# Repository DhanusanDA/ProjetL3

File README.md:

# ProjetL3
Projet de Robotique L3
Cette branche contient les conceptions 3D faites sur SolidWorks pour la structure du robot. Il contient les pièces de support de capteurs et la roue codeuse

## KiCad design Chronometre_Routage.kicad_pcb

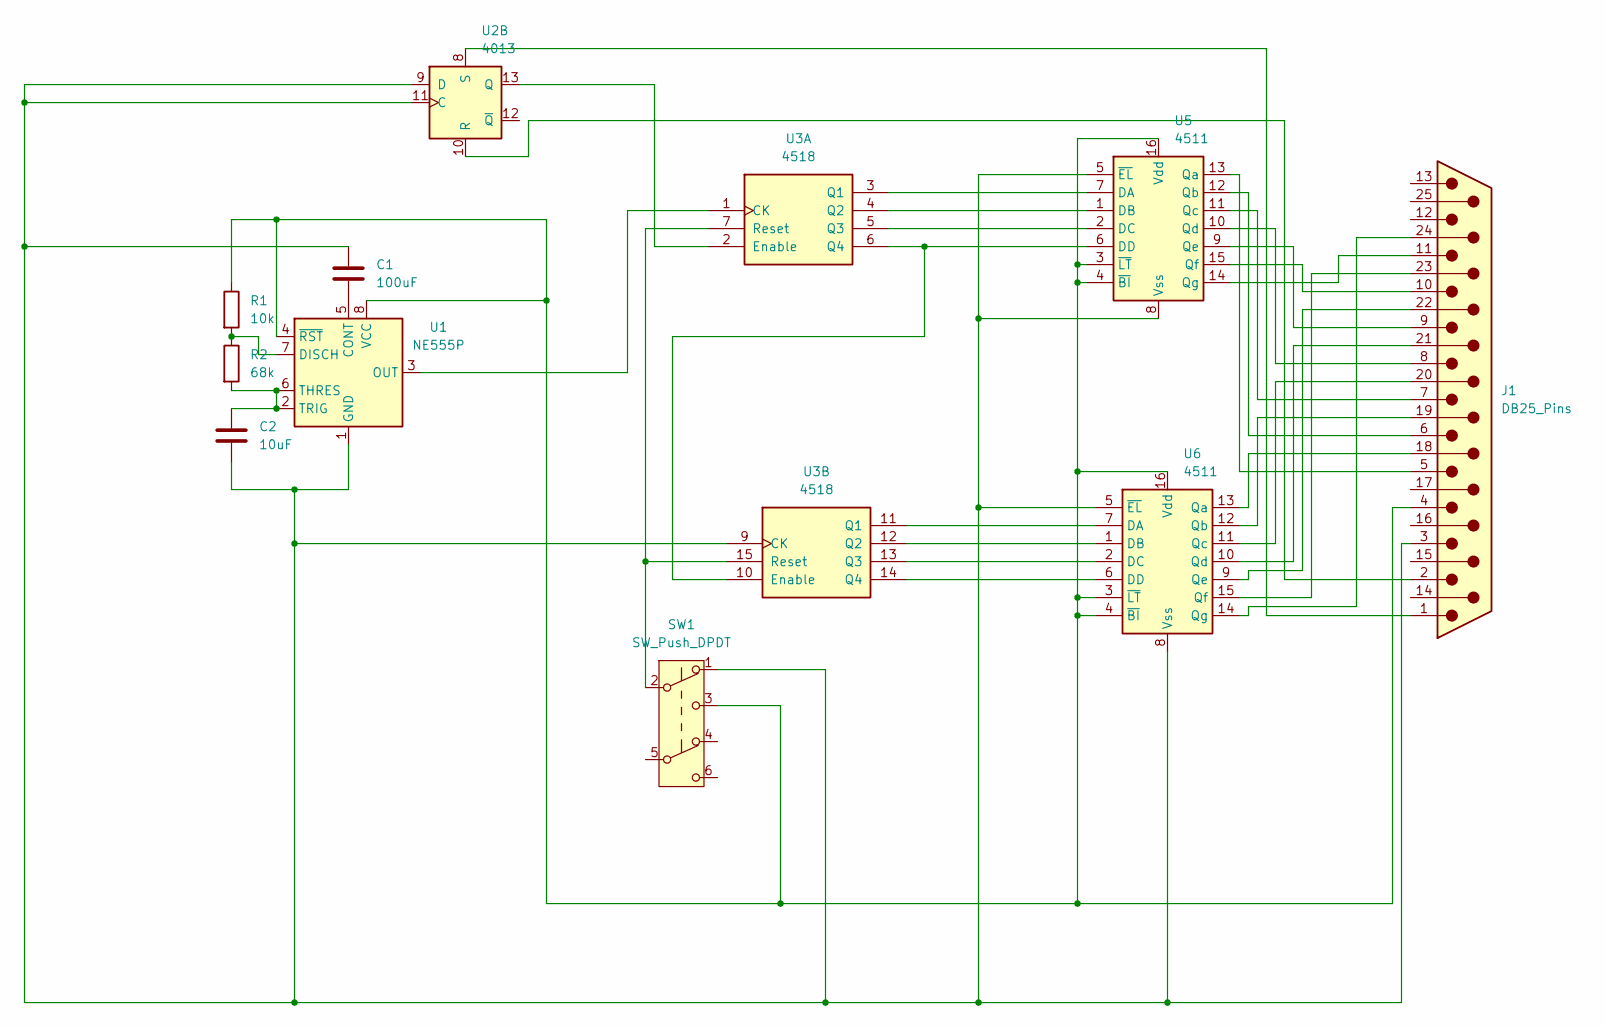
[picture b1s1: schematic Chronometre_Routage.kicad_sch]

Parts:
C1: 100uF; CP_Axial_L10.0mm_D6.0mm_P15.00mm_Horizontal
C2: 10uF; CP_Axial_L10.0mm_D6.0mm_P15.00mm_Horizontal
J1: DB25_Pins; DSUB-25_Socket_Horizontal_P2.77x2.84mm_EdgePinOffset4.94mm_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
R1: 10k; R_Axial_DIN0411_L9.9mm_D3.6mm_P7.62mm_Vertical
R2: 68k; R_Axial_DIN0411_L9.9mm_D3.6mm_P7.62mm_Vertical
SW1: SW_Push_DPDT; SWITCH
U1: NE555P; DIP-8_W7.62mm
U2: 4013; DIP-14_W7.62mm
U3: 4518; DIP-16_W7.62mm
U5, U6: 4511; DIP-16_W7.62mm

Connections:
unnamed: J1.18, U6.13 (Qa)
unnamed: J1.19, U6.12 (Qb)
unnamed: J1.20, U6.11 (Qc)
unnamed: J1.21, U6.10 (Qd)
unnamed: J1.22, U6.9 (Qe)
unnamed: J1.23, U6.15 (Qf)
unnamed: J1.24, U6.14 (Qg)
unnamed: C1.2, U1.5 (CONT)
unnamed: R1.2, R2.1, U1.7 (DISCH)
unnamed: C1.1, C2.2, J1.3, SW1.1 (A), U1.1 (GND), U2.9 (D), U2.11 (C), U3.9 (CK), U5.5 (~EL), U5.8 (Vss), U6.5 (~EL), U6.8 (Vss)
unnamed: U1.3 (OUT), U3.1 (CK)
unnamed: C2.1, R2.2, U1.2 (TRIG), U1.6 (THRES)
unnamed: J1.4, R1.1, SW1.3 (C), U1.4 (~RST), U1.8 (VCC), U5.3 (~LT), U5.4 (~BI), U5.16 (Vdd), U6.3 (~LT), U6.4 (~BI), U6.16 (Vdd)
unnamed: U2.13 (Q), U3.2 (Enable)
unnamed: J1.2, U2.10 (R)
unnamed: J1.1, U2.8 (S)
unnamed: U3.3 (Q1), U5.7 (DA)
unnamed: U3.4 (Q2), U5.1 (DB)
unnamed: U3.5 (Q3), U5.2 (DC)
unnamed: U3.6 (Q4), U3.10 (Enable), U5.6 (DD)
unnamed: SW1.2 (B), U3.7 (Reset), U3.15 (Reset)
unnamed: U3.11 (Q1), U6.7 (DA)
unnamed: U3.12 (Q2), U6.1 (DB)
unnamed: U3.13 (Q3), U6.2 (DC)
unnamed: U3.14 (Q4), U6.6 (DD)
unnamed: J1.5, U5.13 (Qa)
unnamed: J1.6, U5.12 (Qb)
unnamed: J1.7, U5.11 (Qc)
unnamed: J1.8, U5.10 (Qd)
unnamed: J1.9, U5.9 (Qe)
unnamed: J1.10, U5.15 (Qf)
unnamed: J1.11, U5.14 (Qg)

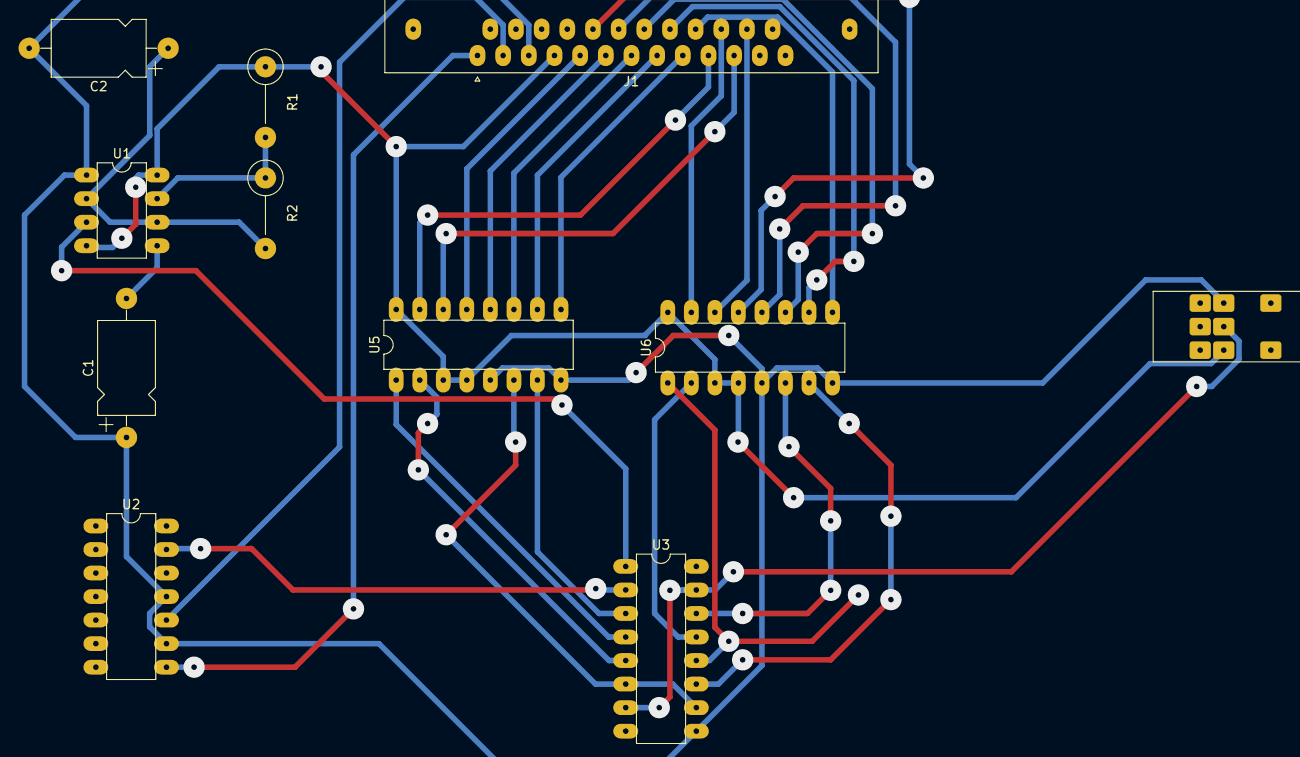
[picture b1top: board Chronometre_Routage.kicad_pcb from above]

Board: 2 copper layers, 11 parts (0 on the bottom side), 32 nets.

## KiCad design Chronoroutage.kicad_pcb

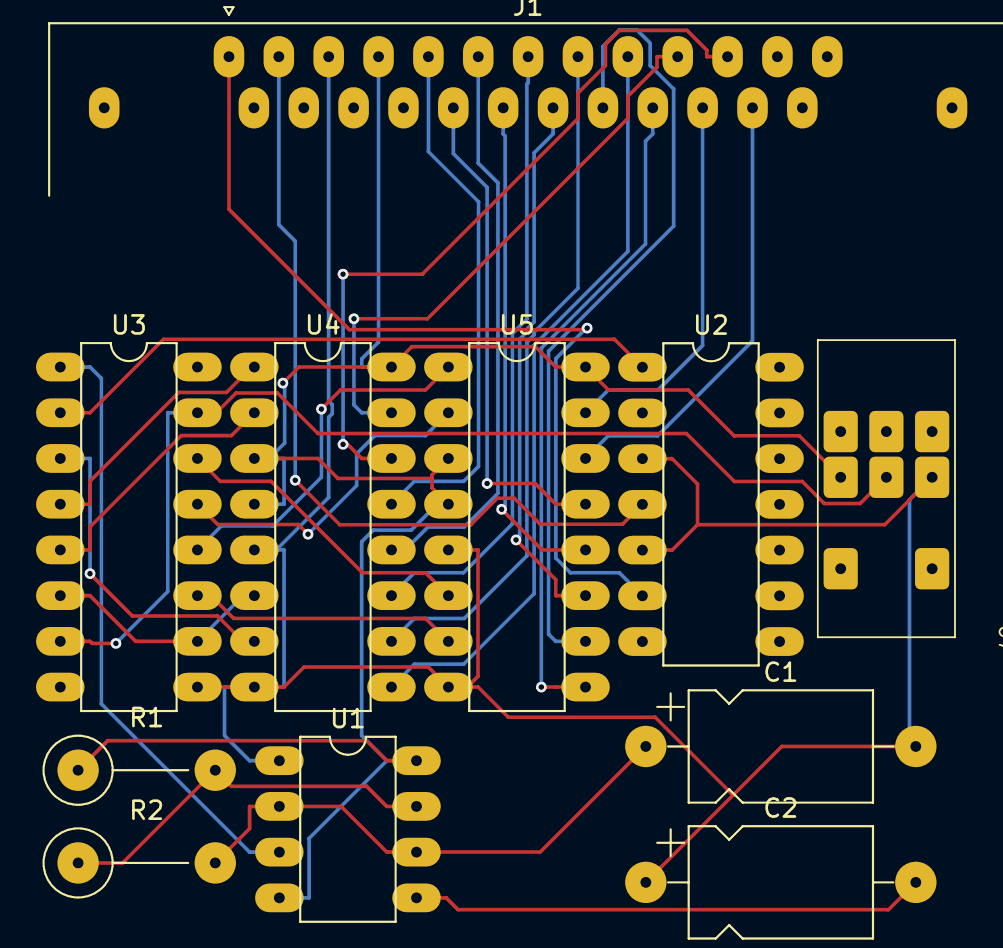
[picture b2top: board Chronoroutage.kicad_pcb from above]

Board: 2 copper layers, 11 parts (0 on the bottom side), 32 nets.

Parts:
C1, C2: 100uF; CP_Axial_L10.0mm_D6.0mm_P15.00mm_Horizontal
J1: DB25_Pins; DSUB-25_Pins_Horizontal_P2.77x2.84mm_EdgePinOffset4.94mm_Ho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
R1: 10k; R_Axial_DIN0411_L9.9mm_D3.6mm_P7.62mm_Vertical
R2: 68k; R_Axial_DIN0411_L9.9mm_D3.6mm_P7.62mm_Vertical
SW1: SW_Push_DPDT; SWITCH
U1: NE555P; DIP-8_W7.62mm
U2: 4013; DIP-14_W7.62mm
U3: 4518; DIP-16_W7.62mm
U4, U5: 4511; DIP-16_W7.62mm

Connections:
+8V: J1.4, R1.1, SW1.3 (C), U1.4 (~RST), U1.8 (VCC), U4.3 (~LT), U4.4 (~BI), U4.16 (Vdd), U5.3 (~LT), U5.4 (~BI), U5.16 (Vdd)
GND: C1.2, C2.1, J1.3, SW1.1 (A), U1.1 (GND), U2.3 (C), U2.5 (D), U3.9 (CK), U4.5 (~EL), U4.8 (Vss), U5.5 (~EL), U5.8 (Vss)
unnamed: J1.18, U5.13 (Qa)
unnamed: J1.19, U5.12 (Qb)
unnamed: J1.20, U5.11 (Qc)
unnamed: J1.21, U5.10 (Qd)
unnamed: J1.22, U5.9 (Qe)
unnamed: J1.23, U5.15 (Qf)
unnamed: J1.24, U5.14 (Qg)
unnamed: C2.2, U1.5 (CONT)
unnamed: R1.2, R2.1, U1.7 (DISCH)
unnamed: U1.3 (OUT), U3.1 (CK)
unnamed: C1.1, R2.2, U1.2 (TRIG), U1.6 (THRES)
unnamed: U2.1 (Q), U3.2 (Enable)
unnamed: J1.2, U2.4 (R)
unnamed: J1.1, U2.6 (S)
unnamed: U3.3 (Q1), U4.7 (DA)
unnamed: U3.4 (Q2), U4.1 (DB)
unnamed: U3.5 (Q3), U4.2 (DC)
unnamed: U3.6 (Q4), U3.10 (Enable), U4.6 (DD)
unnamed: SW1.2 (B), U3.7 (Reset), U3.15 (Reset)
unnamed: U3.11 (Q1), U5.7 (DA)
unnamed: U3.12 (Q2), U5.1 (DB)
unnamed: U3.13 (Q3), U5.2 (DC)
unnamed: U3.14 (Q4), U5.6 (DD)
unnamed: J1.5, U4.13 (Qa)
unnamed: J1.6, U4.12 (Qb)
unnamed: J1.7, U4.11 (Qc)
unnamed: J1.8, U4.10 (Qd)
unnamed: J1.9, U4.9 (Qe)
unnamed: J1.10, U4.15 (Qf)
unnamed: J1.11, U4.14 (Qg)

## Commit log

2026-05-15 Add files via upload
    Ce fichier ;pcb correspond au typon de la carte à tirer. Il a été effectuée avec Free Routing.
2026-05-16 Add files via upload
    Ce nouveau fichier correspond au routage de notre montage manuellement. Comparé à l'ancien fichier, le routage n'a pas été fait par logiciel. J'attend la decision du professeur afin de savoir lequel 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
2026-05-16 Add files via upload
    Ce fichier est le Schematic du montage qui correspond au chronométrage avec le logiciel KiCad. Ce montage a directement été validé par les intervenants. Il correspond a mon montage déjà effectué sur 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
2026-05-18 Add files via upload
    Code pour le suivi de ligne
2026-05-19 changement
    Modification du système de vitesse ajout de petite et grande vitesse pour gérer le suivi de ligne et les virages
2026-05-20 Add files via upload
    Ajout de programme de gestion ultrasons et servomoteur
2026-05-20 Create Evitement_Obstacle_SuiviLigne
    Le premier code pour l'evitement d'obstacle avec le suivi de ligne
2026-05-20 Create Evitement_Obstacle
    Programme pour l'évitement d'obstacle, il complète le précedent
2026-05-21 Add files via upload
    Chrono validé le 20/05/2026
2026-05-21 Squelette V1
    Ajout du squelette du programme du robot suiveur de ligne + implémentation des fonction : suivi de ligne, détection de couleur, traversée du tunnel et pilotage du moteur
2026-05-21 Code Exemple pour encodeur
2026-05-22 Add files via upload
    Plan d'expérience pour les lancers de balle avec la catapulte.
2026-05-22 Fonction Evitement Obstacle
2026-05-22 Create TestAffichageDemiTour
    Fichier pour tester uniquement la partie du demi tour et de l'affichage couleur
2026-05-22 Update TestAffichageDemiTour
    Nouveau Test pour afficher la couleur et faire demi tour, nous allons utiliser le capteur ultrason pour détecter l'etape
2026-05-22 Add files via upload
    passerelle sous rdm6
2026-05-23 Add files via upload
    Ces deux images sont les schemas réel et imprimés du circuit de chronomètre
2026-05-23 Squelette V2
    - Modification de la détection de couleur
    - Ajout des fonction d'évitement d'obstacle, de récupération de ligne, de demi tour et d'affiche de la distance
    - implémentation de ces fonction dans le main jusqu'à la section 7
2026-05-26 Add files via upload
    Modification de paramètres de vitesse
2026-05-27 Add files via upload
    ajout d'une fonction pour piloter les moteur de la catapultes
2026-05-28 version finale (Je l'espère)
2026-05-29 Add files via upload
    Version finale du circuit imprimé fait sur KiCad.
2026-05-29 Add files via upload
    Version finale du schématique fait sur KiCad
2026-05-29 Update README.md
    Mise à jour du fichier Read.me
2026-05-29 Update README.md
    Mise à jour des informations présentes dans la branche Design_Coque
2026-05-29 Update README.md
    Mise à jour des informations contenant ce fichier
2026-05-29 Update README.md
    Mise à jour des informations des fichiers présents dans cette branche
